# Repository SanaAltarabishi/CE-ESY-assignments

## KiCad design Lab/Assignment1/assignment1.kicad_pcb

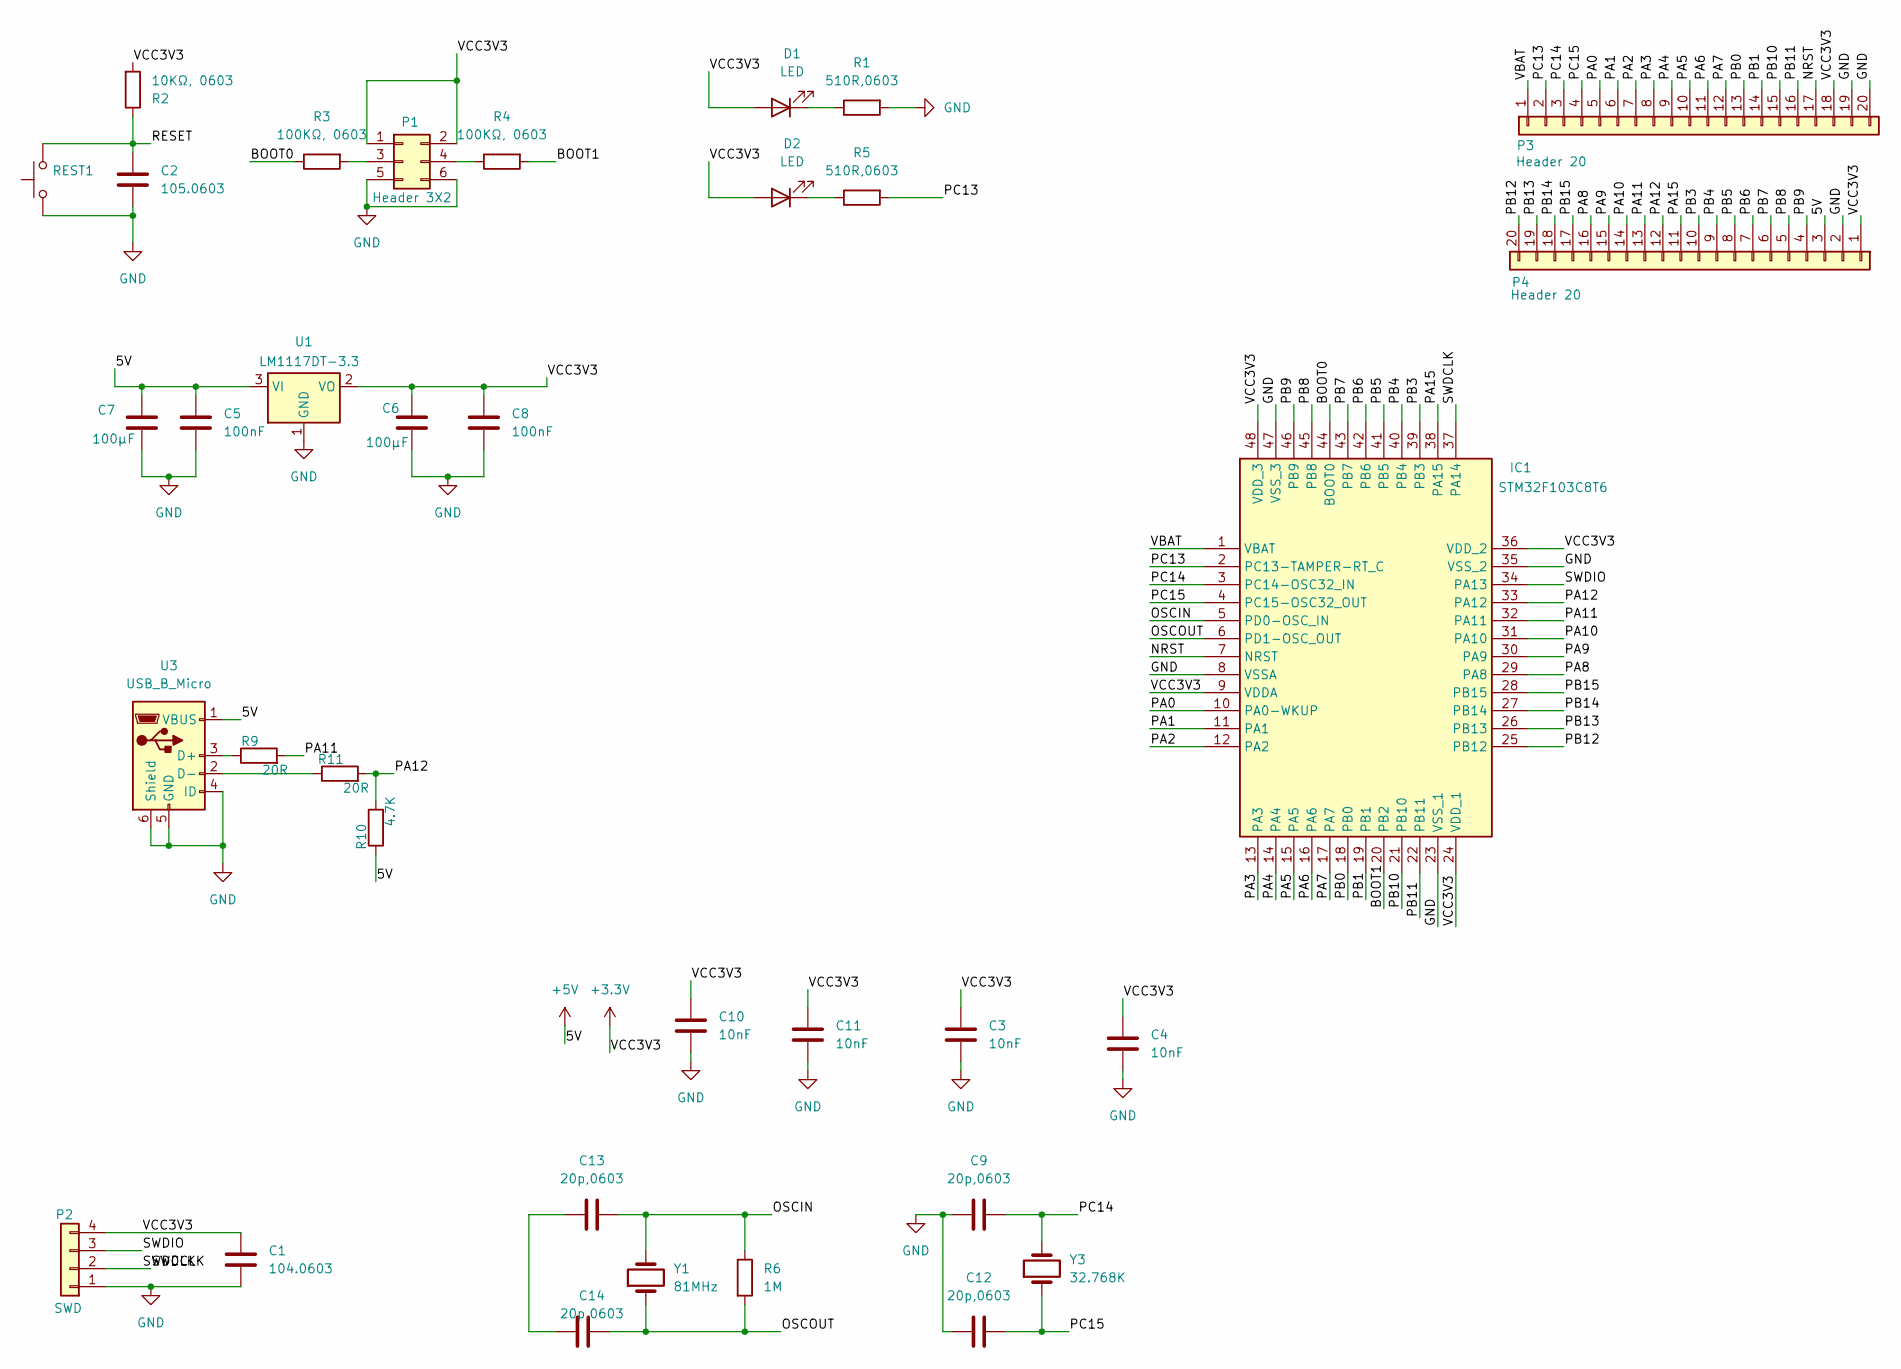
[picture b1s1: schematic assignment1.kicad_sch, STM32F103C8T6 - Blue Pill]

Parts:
C1: 104.0603; C_0603_1608Metric
C2: 105.0603; C_0603_1608Metric
C3, C4, C10, C11: 10nF; C_0603_1608Metric
C5, C8: 100nF; C_0603_1608Metric
C6, C7: 100µF; C_0603_1608Metric
C9, C12, C13, C14: 20p,0603; C_0603_1608Metric
D1, D2: LED; LED_0603_1608Metric
IC1: STM32F103C8T6; LQFP-48_7x7mm_P0.5mm; Manufacturer_Part_Number STM32F103C8T6; Mouser Part Number 511-STM32F103C8T6
P1: Header 3X2; PinHeader_2x03_P2.54mm_Vertical
P2: SWD; PinHeader_1x04_P2.54mm_Vertical
P3, P4: Header 20; PinHeader_1x20_P2.54mm_Vertical
R1, R5: 510R,0603; R_0603_1608Metric
R2: 10KΩ, 0603; R_0603_1608Metric
R3, R4: 100KΩ, 0603; R_0603_1608Metric
R6: 1M; R_0603_1608Metric
R9, R11: 20R; R_0603_1608Metric
R10: 4.7K; R_0603_1608Metric
REST1: SW_SPST_TL3342
U1: LM1117DT-3.3; TO-252-3_TabPin2
U3: USB_B_Micro; USB_Micro-B_Molex-105017-0001
Y1: 81MHz; Crystal_SMD_3225-4Pin_3.2x2.5mm
Y3: 32.768K; Crystal_SMD_3225-4Pin_3.2x2.5mm

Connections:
+3.3V: C1.1, C3.1, C4.1, C6.1, C8.1, C10.1, C11.1, D1.2 (A), D2.2 (A), IC1.9 (VDDA), IC1.24 (VDD_1), IC1.36 (VDD_2), IC1.48 (VDD_3), P1.1, P1.2, P2.4, P3.18, P4.1, R2.2, U1.2 (VO)
+5V: C5.1, C7.1, P4.3, R10.1, U1.3 (VI), U3.1 (VBUS)
/BOOT0: IC1.44 (BOOT0), R3.1
/BOOT1: IC1.20 (PB2), R4.2
/NRST: IC1.7 (NRST), P3.17
/OSCIN: C13.2, IC1.5 (PD0-OSC_IN), R6.1, Y1.2
/OSCOUT: C14.2, IC1.6 (PD1-OSC_OUT), R6.2, Y1.1
/PA0: IC1.10 (PA0-WKUP), P3.5
/PA1: IC1.11 (PA1), P3.6
/PA2: IC1.12 (PA2), P3.7
/PA3: IC1.13 (PA3), P3.8
/PA4: IC1.14 (PA4), P3.9
/PA5: IC1.15 (PA5), P3.10
/PA6: IC1.16 (PA6), P3.11
/PA7: IC1.17 (PA7), P3.12
/PA8: IC1.29 (PA8), P4.16
/PA9: IC1.30 (PA9), P4.15
/PA10: IC1.31 (PA10), P4.14
/PA11: IC1.32 (PA11), P4.13, R9.2
/PA12: IC1.33 (PA12), P4.12, R10.2, R11.2
/PA15: IC1.38 (PA15), P4.11
/PB0: IC1.18 (PB0), P3.13
/PB1: IC1.19 (PB1), P3.14
/PB3: IC1.39 (PB3), P4.10
/PB4: IC1.40 (PB4), P4.9
/PB5: IC1.41 (PB5), P4.8
/PB6: IC1.42 (PB6), P4.7
/PB7: IC1.43 (PB7), P4.6
/PB8: IC1.45 (PB8), P4.5
/PB9: IC1.46 (PB9), P4.4
/PB10: IC1.21 (PB10), P3.15
/PB11: IC1.22 (PB11), P3.16
/PB12: IC1.25 (PB12), P4.20
/PB13: IC1.26 (PB13), P4.19
/PB14: IC1.27 (PB14), P4.18
/PB15: IC1.28 (PB15), P4.17
/PC13: IC1.2 (PC13-TAMPER-RT_C), P3.2, R5.2
/PC14: C9.2, IC1.3 (PC14-OSC32_IN), P3.3, Y3.2
/PC15: C12.2, IC1.4 (PC15-OSC32_OUT), P3.4, Y3.1
/RESET: C2.1, R2.1, REST1.2
/SWDCLK: IC1.37 (PA14), P2.2
/SWDIO: IC1.34 (PA13), P2.3
/VBAT: IC1.1 (VBAT), P3.1
GND: C1.2, C2.2, C3.2, C4.2, C5.2, C6.2, C7.2, C8.2, C9.1, C10.2, C11.2, C12.1, IC1.8 (VSSA), IC1.23 (VSS_1), IC1.35 (VSS_2), IC1.47 (VSS_3), P1.5, P1.6, P2.1, P3.19, P3.20, P4.2, R1.2, REST1.1, U1.1 (GND), U3.4 (ID), U3.5 (GND), U3.6 (Shield)
unnamed: C13.1, C14.1
unnamed: D1.1 (K), R1.1
unnamed: D2.1 (K), R5.1
unnamed: P1.3, R3.2
unnamed: P1.4, R4.1
unnamed: R9.1, U3.3 (D+)
unnamed: R11.1, U3.2 (D-)

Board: 2 copper layers, 35 parts (0 on the bottom side), 51 nets, no tracks yet.

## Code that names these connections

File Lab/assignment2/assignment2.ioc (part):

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Mcu.Name=STM32F103C(8-B)Tx
Mcu.Package=LQFP48
Mcu.UserName=STM32F103C8Tx
PA0-WKUP.GPIOParameters=GPIO_PuPd,GPIO_Label
PA0-WKUP.GPIO_Label=BTN1
PA0-WKUP.GPIO_PuPd=GPIO_PULLDOWN
PA0-WKUP.Signal=GPIO_Input
PA1.GPIOParameters=GPIO_PuPd,GPIO_Label
PA1.GPIO_Label=BTN2
PA1.GPIO_PuPd=GPIO_PULLUP
PA1.Signal=GPIO_Input
PA2.GPIOParameters=GPIO_PuPd,GPIO_Label
PA2.GPIO_Label=BTN3
PA2.GPIO_PuPd=GPIO_PULLUP
PA2.Signal=GPIO_Input
PB0.GPIOParameters=GPIO_Label
PB0.GPIO_Label=Motor
PB0.Signal=GPIO_Output
PB10.Mode=I2C
PB10.Signal=I2C2_SCL
PB11.Mode=I2C
PB11.Signal=I2C2_SDA
board=custom

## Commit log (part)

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2026-04-27 Add Assignment1 - Circular Buffer
2026-05-25 solving lab homework with kicad
